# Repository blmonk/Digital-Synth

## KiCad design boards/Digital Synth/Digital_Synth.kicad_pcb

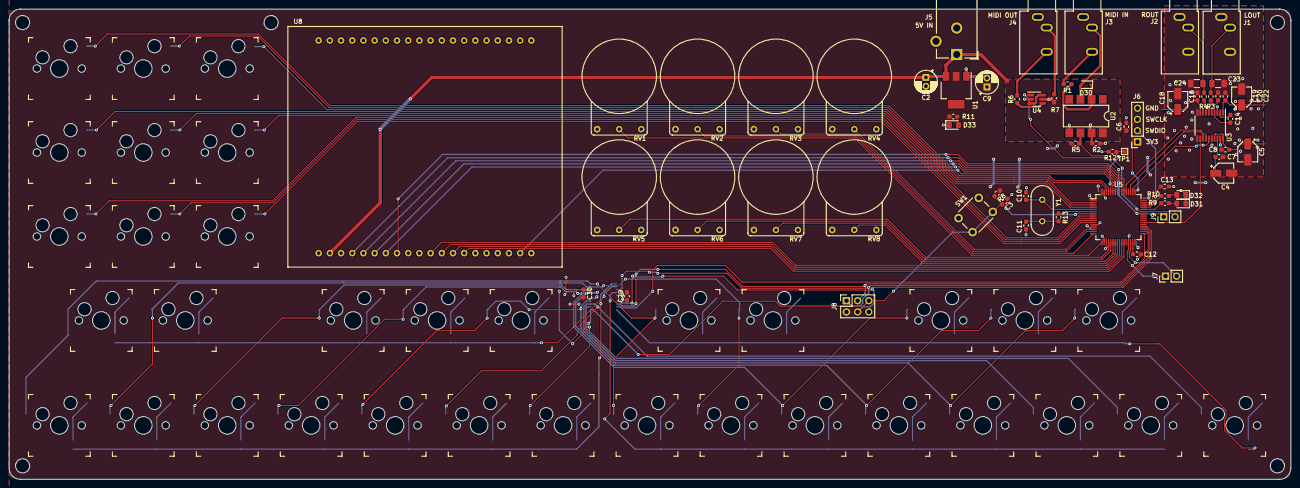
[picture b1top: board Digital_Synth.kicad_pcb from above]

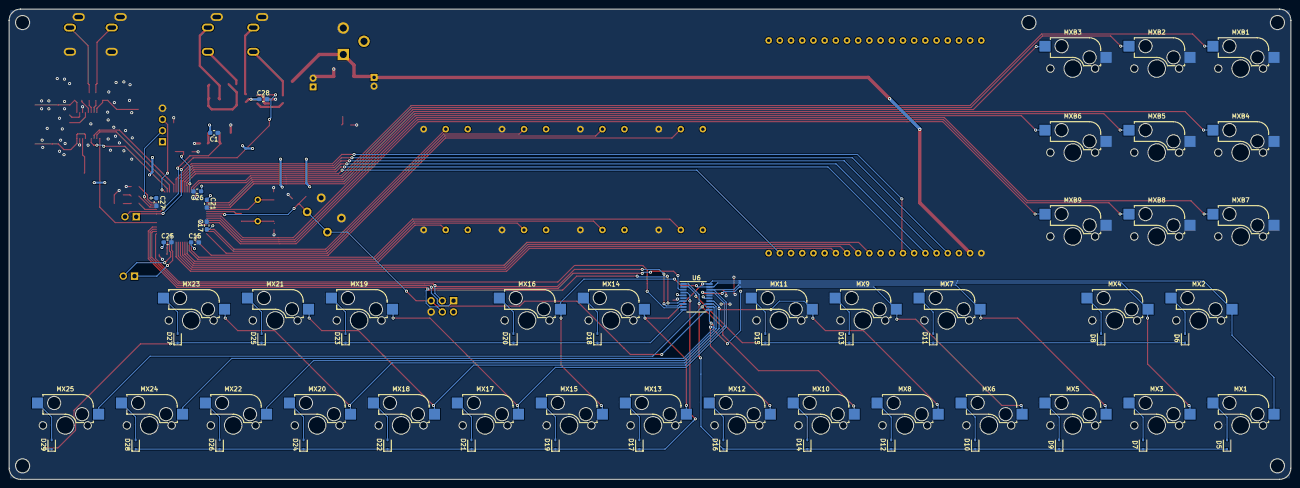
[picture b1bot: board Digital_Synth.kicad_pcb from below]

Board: 2 copper layers, 290.8 x 106.7 mm, 133 parts (34 on the bottom side), 108 nets.

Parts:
C1, C3, C6, C7, C8, C15, C16, C17, C20, C21, C25, C26, C27, C28, C29, C30: 0.1uF; C_0603_1608Metric_Pad1.05x0.95mm_HandSolder
C2, C9: 10uF; CP_Radial_D5.0mm_P2.00mm
C4, C5, C18, C22: 10uF; CP_Elec_4x5.8
C10, C11: 22pF; C_0603_1608Metric_Pad1.05x0.95mm_HandSolder
C12, C13, C14, C19: 2.2uF; C_0603_1608Metric_Pad1.05x0.95mm_HandSolder
C23, C24: 2.2nF; C_1206_3216Metric
D5, D6, D7, D8, D9, D10, D11, D12, D13, D14, D15, D16, D17, D18, D19, D20, D21, D22, D23, D24, D25, D26, D27, D28, D29: D_Small; D_SOD-323
D30: 1N4148; D_SOD-323
D31, D32, D33: Green; D_0805_2012Metric_Pad1.15x1.40mm_HandSolder
J1: LOUT; Jack_3.5mm_CUI_SJ1-3533NG_Horizontal
J2: ROUT; Jack_3.5mm_CUI_SJ1-3533NG_Horizontal
J3: MIDI IN; Jack_3.5mm_CUI_SJ1-3533NG_Horizontal
J4: MIDI OUT; Jack_3.5mm_CUI_SJ1-3533NG_Horizontal
J5: 5V IN; BarrelJack_CUI_PJ-102AH_Horizontal
J6: JTAG; PinSocket_1x04_P2.54mm_Vertical
J7: UART_Debug; PinHeader_1x02_P2.54mm_Vertical
J8: ISP; PinSocket_2x03_P2.54mm_Vertical
J9: UART_MIDI; PinHeader_1x02_P2.54mm_Vertical
MX1: C3; Kailh_socket_MX
MX2: C#3; Kailh_socket_MX
MX3: D3; Kailh_socket_MX
MX4: D#3; Kailh_socket_MX
MX5: E3; Kailh_socket_MX
MX6: F3; Kailh_socket_MX
MX7: F#3; Kailh_socket_MX
MX8: G3; Kailh_socket_MX
MX9: G#3; Kailh_socket_MX
MX10: A4; Kailh_socket_MX
MX11, MX23: A#4; Kailh_socket_MX
MX12: B4; Kailh_socket_MX
MX13: C4; Kailh_socket_MX
MX14: C#4; Kailh_socket_MX
MX15: D4; Kailh_socket_MX
MX16: D#4; Kailh_socket_MX
MX17: E4; Kailh_socket_MX
MX18: F4; Kailh_socket_MX
MX19: F#4; Kailh_socket_MX
MX20: G4; Kailh_socket_MX
MX21: G#4; Kailh_socket_MX
MX22: A5; Kailh_socket_MX
MX24: B5; Kailh_socket_MX
MX25: C5; Kailh_socket_MX
MXB1, MXB2, MXB3, MXB4, MXB5, MXB6, MXB7, MXB8, MXB9: SW_Push; Kailh_socket_MX
R1, R6, R7: 220; R_0603_1608Metric_Pad1.05x0.95mm_HandSolder
R2: 10k; R_0603_1608Metric_Pad1.05x0.95mm_HandSolder
R3, R4, R9, R10, R11: 470; R_0603_1608Metric_Pad1.05x0.95mm_HandSolder
R5: 1k; R_0603_1608Metric_Pad1.05x0.95mm_HandSolder
R8: 4.7k; R_0603_1608Metric_Pad1.05x0.95mm_HandSolder
R12: 100k; R_0603_1608Metric_Pad1.05x0.95mm_HandSolder
R13: R_Small; R_0603_1608Metric_Pad1.05x0.95mm_HandSolder
RV1, RV2, RV3, RV4, RV5, RV6, RV7, RV8: 10k; Hiletgo
SW1: SW_Push; SW_PUSH_6mm
TP1: TestPoint; TestPoint_Pad_1.0x1.0mm
U1: LM1117-3.3; SOT-223
U2: 6N138; SMDIP-8_W7.62mm
U3: PCM5101A; TSSOP-20_4.4x6.5mm_P0.65mm
U4: SN74LVC2G14; SOT-23-6_Handsoldering
U5: STM32F405RGTx; LQFP-64_10x10mm_P0.5mm
U6: ATtiny167-XU; TSSOP-20_4.4x6.5mm_P0.65mm
U8: Adafruit_2.4in
Y1: 8MHz; Crystal_HC49-U_Vertical

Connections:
+3V3: C5.1, C6.2, C8.2, C9.1, C15.1, C16.2, C17.1, C18.1, C20.2, C21.1, C22.1, C25.1, C26.1, C27.1, C29.2, C30.2, J6.1, J8.2, R5.1, R8.1, R11.1, RV1.1, RV2.1, RV3.1, RV4.1, RV5.1, RV6.1, RV7.1, RV8.1, U1.2, U3.1, U3.8, U3.17, U3.20, U5.1, U5.13, U5.19, U5.32, U5.48, U5.64, U6.5, U6.15
+5V: C1.2, C2.1, C28.1, J5.1, R7.1, U1.3, U2.8, U4.5, U8.2
B1: MXB1.1, U5.61
B2: MXB2.1, U5.62
B3: MXB3.1, U5.2
B4: MXB4.1, U5.3
B5: MXB5.1, U5.4
B6: MXB6.1, U5.8
B7: MXB7.1, U5.9
B8: MXB8.1, U5.10
B9: MXB9.1, U5.11
BCK: U3.13, U5.51
DC: U5.54, U8.8
GND: C1.1, C2.2, C3.1, C4.2, C5.2, C6.1, C7.2, C8.1, C9.2, C10.2, C11.2, C12.2, C13.2, C15.2, C16.1, C17.2, C18.2, C19.2, C20.1, C21.2, C22.2, C23.1, C24.1, C25.2, C26.2, C27.2, C28.2, C29.1, C30.1, D31.1, D32.1, D33.1, J1.R, J1.S, J2.R, J2.S, J3.S, J4.S, J5.2, J6.4, J8.6, MXB1.2, MXB2.2, MXB3.2, MXB4.2, MXB5.2, MXB6.2, MXB7.2, MXB8.2, MXB9.2, R2.2, R12.2, RV1.3, RV2.3, RV3.3, RV4.3, RV5.3, RV6.3, RV7.3, RV8.3, SW1.2, U1.1, U2.5, U3.3, U3.9, U3.10, U3.11, U3.16, U3.19, U4.2, U5.12, U5.18, U5.63, U6.6, U6.16, U8.1
LRCLK: U3.15, U5.50
MCK: U3.12, U5.38
NRST: C3.2, J8.5, R8.2, SW1.1, U5.7, U6.11
unnamed: C4.1, C7.1, U3.18
unnamed: C10.1, U5.5, Y1.1
unnamed: C11.1, R13.2, Y1.2
unnamed: C12.1, U5.31
unnamed: C13.1, U5.47
unnamed: C14.1, U3.4
unnamed: C14.2, U3.2
unnamed: C19.1, U3.5
unnamed: C23.2, J1.T, R3.1
unnamed: C24.2, J2.T, R4.1
unnamed: D5.2, MX1.1
unnamed: D6.2, MX2.1
unnamed: D7.2, MX3.1
unnamed: D8.2, MX4.1
unnamed: D9.2, MX5.1
unnamed: D10.2, MX6.1
unnamed: D11.2, MX7.1
unnamed: D12.2, MX8.1
unnamed: D13.2, MX9.1
unnamed: D14.2, MX10.1
unnamed: D15.2, MX11.1
unnamed: D16.2, MX12.1
unnamed: D17.2, MX13.1
unnamed: D18.2, MX14.1
unnamed: D19.2, MX15.1
unnamed: D20.2, MX16.1
unnamed: D21.2, MX17.1
unnamed: D22.2, MX18.1
unnamed: D23.2, MX19.1
unnamed: D24.2, MX20.1
unnamed: D25.2, MX21.1
unnamed: D26.2, MX22.1
unnamed: D27.2, MX23.1
unnamed: D28.2, MX24.1
unnamed: D29.2, MX25.1
unnamed: D30.1, R1.1, U2.2
unnamed: D30.2, J3.T, U2.3
unnamed: D31.2, R9.2
unnamed: D32.2, R10.2
unnamed: D33.2, R11.2
unnamed: J3.R, R1.2
unnamed: J4.R, R6.1
unnamed: J4.T, R7.2
unnamed: R2.1, U2.7
unnamed: R3.2, U3.6
unnamed: R4.2, U3.7
unnamed: R6.2, U4.4
unnamed: R9.1, U5.44
unnamed: R10.1, U5.45
unnamed: R12.1, TP1.1, U5.60
unnamed: R13.1, U5.6
unnamed: U4.3, U4.6
RV1: RV1.2, U5.17
RV2: RV2.2, U5.16
RV3: RV3.2, U5.15
RV4: RV4.2, U5.14
RV5: RV5.2, U5.20
RV6: RV6.2, U5.21
RV7: RV7.2, U5.22
RV8: RV8.2, U5.23
RX_Debug: J7.2, U5.30
RX_MIDI: J9.2, R5.2, U2.6, U5.43
SD: U3.14, U5.53
SPI1_CS1: U5.59, U8.19
SPI1_CS2: U5.58, U8.7
SPI1_MISO: U5.56, U8.5
SPI1_MOSI: U5.57, U8.6
SPI1_SCK: U5.55, U8.4
SPI2_CS: U5.33, U6.9
SPI2_MISO: J8.1, U5.35, U6.3
SPI2_MOSI: J8.4, U5.36, U6.7
SPI2_SCK: J8.3, U5.34, U6.8
SWCLK: J6.3, U5.49
SWDIO: J6.2, U5.46
TX_Debug: J7.1, U5.29
TX_MIDI: J9.1, U4.1, U5.42
X+: U5.25, U8.12
X-: U5.27, U8.14
Y+: U5.24, U8.11
Y-: U5.26, U8.13
col0: MX1.2, MX2.2, MX13.2, MX14.2, U6.20
col1: MX3.2, MX4.2, MX15.2, MX16.2, U6.19
col2: MX5.2, MX7.2, MX17.2, MX19.2, U6.18
col3: MX6.2, MX9.2, MX18.2, MX21.2, U6.17
col4: MX8.2, MX11.2, MX20.2, MX23.2, U6.14
col5: MX10.2, MX22.2, MX25.2, U6.13
col6: MX12.2, MX24.2, U6.12
row0: D5.1, D7.1, D9.1, D10.1, D12.1, D14.1, D16.1, U6.1
row1: D6.1, D8.1, D11.1, D13.1, D15.1, U6.2
row2: D17.1, D19.1, D21.1, D22.1, D24.1, D26.1, D28.1, U6.4
row3: D18.1, D20.1, D23.1, D25.1, D27.1, D29.1, U6.10

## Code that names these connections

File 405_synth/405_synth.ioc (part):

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Mcu.Name=STM32F405RGTx
Mcu.Package=LQFP64
Mcu.UserName=STM32F405RGTx
PA0-WKUP.GPIOParameters=GPIO_Label
PA0-WKUP.GPIO_Label=RV4
PA0-WKUP.Signal=ADCx_IN0
PA1.GPIOParameters=GPIO_Label
PA1.GPIO_Label=RV3
PA1.Signal=ADCx_IN1
PA10.Mode=Asynchronous
PA10.Signal=USART1_RX
PA11.GPIOParameters=GPIO_Label
PA11.GPIO_Label=STAT_LED2
PA11.Signal=GPIO_Output
PA12.GPIOParameters=GPIO_Label
PA12.GPIO_Label=STAT_LED1
PA12.Signal=GPIO_Output
PA13.Mode=Serial_Wire
PA13.Signal=SYS_JTMS-SWDIO
PA14.Mode=Serial_Wire
PA14.Signal=SYS_JTCK-SWCLK
PA15.Mode=Half_Duplex_Master
PA15.Signal=I2S3_WS
PA2.GPIOParameters=GPIO_Label
PA2.GPIO_Label=RV2
PA2.Signal=ADCx_IN2
PA3.GPIOParameters=GPIO_Label
PA3.GPIO_Label=RV1
PA3.Signal=ADCx_IN3
PA4.GPIOParameters=GPIO_Label
PA4.GPIO_Label=RV5
PA4.Signal=ADCx_IN4
PA5.GPIOParameters=GPIO_Label
PA5.GPIO_Label=RV6
PA5.Signal=ADCx_IN5
PA6.GPIOParameters=GPIO_Label
PA6.GPIO_Label=RV7
PA6.Signal=ADCx_IN6
PA7.GPIOParameters=GPIO_Label
PA7.GPIO_Label=RV8
PA7.Signal=ADCx_IN7
PA9.Mode=Asynchronous
PA9.Signal=USART1_TX
PB0.GPIOParameters=GPIO_Label
PB0.GPIO_Label=Y-
PB0.Signal=ADCx_IN8
PB1.GPIOParameters=GPIO_Label
PB1.GPIO_Label=X-
PB1.Signal=ADCx_IN9
PB10.Mode=Asynchronous
PB10.Signal=USART3_TX
PB11.Mode=Asynchronous
PB11.Signal=USART3_RX
PB12.GPIOParameters=GPIO_Label
PB12.GPIO_Label=SPI2_CS
PB12.Signal=GPIO_Output
PB13.Mode=Full_Duplex_Master
PB13.Signal=SPI2_SCK
PB14.Mode=Full_Duplex_Master
PB14.Signal=SPI2_MISO
PB15.Mode=Full_Duplex_Master
PB15.Signal=SPI2_MOSI
PB3.Mode=Full_Duplex_Master
PB3.Signal=SPI1_SCK
PB4.Mode=Full_Duplex_Master
PB4.Signal=SPI1_MISO
PB5.Mode=Full_Duplex_Master
PB5.Signal=SPI1_MOSI
PB6.GPIOParameters=GPIO_Label
PB6.GPIO_Label=SPI1_CS2
PB6.Signal=GPIO_Output
PB7.GPIOParameters=GPIO_Label
PB7.GPIO_Label=SPI1_CS1
PB7.Signal=GPIO_Output
PB8.GPIOParameters=GPIO_PuPd,GPIO_Label
PB8.GPIO_Label=B1
PB8.GPIO_PuPd=GPIO_PULLUP
PB8.Signal=GPIO_Input
PB9.GPIOParameters=GPIO_Label
PB9.GPIO_Label=B2
PB9.Signal=GPIO_Input
PC0.GPIOParameters=GPIO_Label
PC0.GPIO_Label=B6
PC0.Signal=GPIO_Input
PC1.GPIOParameters=GPIO_Label
PC1.GPIO_Label=B7
PC1.Signal=GPIO_Input
PC10.Mode=Half_Duplex_Master
PC10.Signal=I2S3_CK
PC12.Mode=Half_Duplex_Master
PC12.Signal=I2S3_SD
PC13-ANTI_TAMP.GPIOParameters=GPIO_Label
PC13-ANTI_TAMP.GPIO_Label=B3
PC13-ANTI_TAMP.Signal=GPIO_Input
PC14-OSC32_IN.GPIOParameters=GPIO_Label
PC14-OSC32_IN.GPIO_Label=B4
PC14-OSC32_IN.Signal=GPIO_Input
PC15-OSC32_OUT.GPIOParameters=GPIO_Label
PC15-OSC32_OUT.GPIO_Label=B5
PC15-OSC32_OUT.Signal=GPIO_Input
PC2.GPIOParameters=GPIO_Label
PC2.GPIO_Label=B8
PC2.Signal=GPIO_Input
PC3.GPIOParameters=GPIO_Label
PC3.GPIO_Label=B9
PC3.Signal=GPIO_Input
PC4.GPIOParameters=GPIO_Label
PC4.GPIO_Label=Y+
PC4.Signal=ADCx_IN14
PC5.GPIOParameters=GPIO_Label
PC5.GPIO_Label=X+
PC5.Signal=ADCx_IN15
PC7.Mode=Master_Clock_Activated
PC7.Signal=I2S3_MCK
PD2.GPIOParameters=GPIO_Label
PD2.GPIO_Label=DC
PD2.Signal=GPIO_Output
PH0-OSC_IN.GPIOParameters=GPIO_Label
PH0-OSC_IN.GPIO_Label=RCC_OSC_IN
PH0-OSC_IN.Mode=HSE-External-Oscillator
PH0-OSC_IN.Signal=RCC_OSC_IN
PH1-OSC_OUT.Mode=HSE-External-Oscillator
PH1-OSC_OUT.Signal=RCC_OSC_OUT
RCC.HSE_VALUE=8000000
RCC.SYSCLKFreq_VALUE=168000000
RCC.SYSCLKSource=RCC_SYSCLKSOURCE_PLLCLK
board=custom

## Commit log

2022-02-04 added kicad project
2022-02-05 progress on layout for DAC and MIDI
2022-03-16 laid out keyboard
2022-03-18 finished routing to avr
2022-03-18 added display
2022-04-06 almost done with layout
2022-04-07 finished layout
